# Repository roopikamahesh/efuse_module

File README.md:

# efuse_module
efuse + tvs diode

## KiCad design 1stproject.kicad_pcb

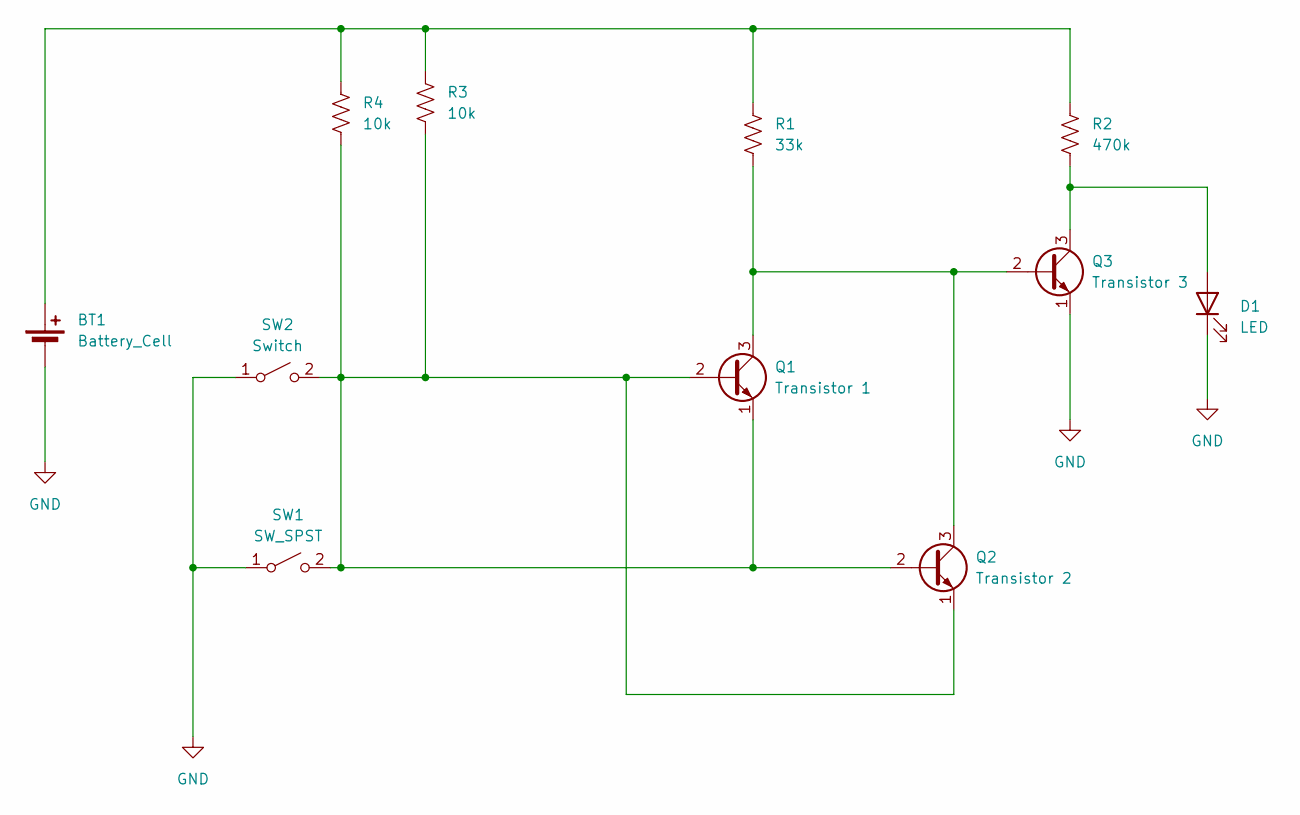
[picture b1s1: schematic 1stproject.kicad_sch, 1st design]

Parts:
BT1: Battery_Cell; BatteryHolder_LINX_BAT-HLD-012-SMT
D1: LED; LED_D5.0mm
Q1: Transistor 1; TO-92
Q2: Transistor 2; TO-92
Q3: Transistor 3; TO-92
R1: 33k; R_Axial_DIN0309_L9.0mm_D3.2mm_P12.70mm_Horizontal
R2: 470k; R_Axial_DIN0309_L9.0mm_D3.2mm_P12.70mm_Horizontal
R3, R4: 10k; R_Axial_DIN0309_L9.0mm_D3.2mm_P12.70mm_Horizontal
SW1: SW_SPST; SW_PUSH_6mm
SW2: Switch; SW_PUSH_6mm

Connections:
GND: BT1.2 (-), D1.1 (K), Q3.1 (E), SW1.1 (A), SW2.1 (A)
unnamed: BT1.1 (+), R1.1, R2.1, R3.1, R4.1
unnamed: D1.2 (A), Q3.3 (C), R2.2
unnamed: Q1.1 (E), Q1.2 (B), Q2.1 (E), Q2.2 (B), R3.2, R4.2, SW1.2 (B), SW2.2 (B)
unnamed: Q1.3 (C), Q2.3 (C), Q3.2 (B), R1.2

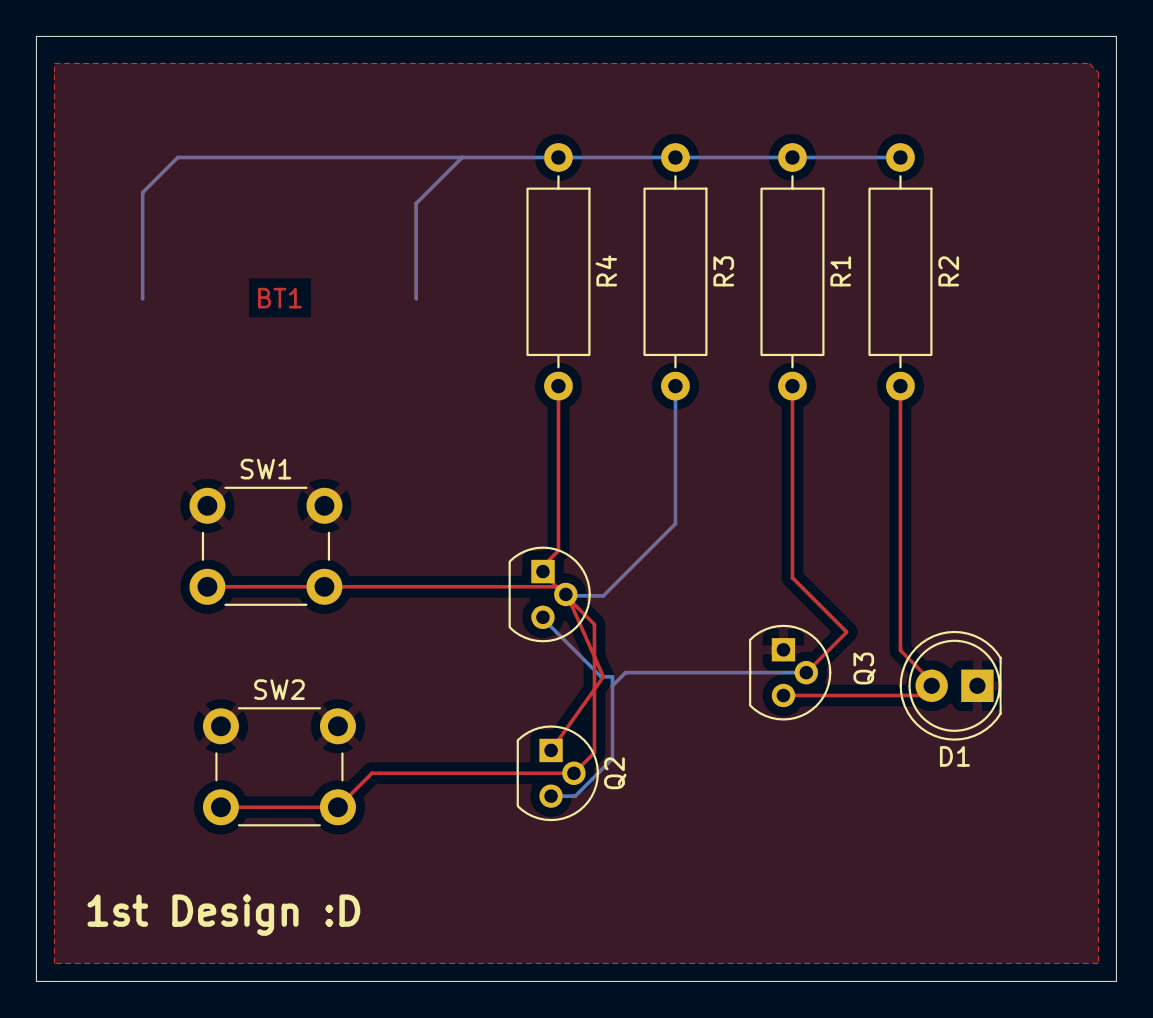
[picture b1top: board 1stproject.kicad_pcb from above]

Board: 2 copper layers, 60.0 x 52.5 mm, 11 parts (1 on the bottom side), 5 nets.
